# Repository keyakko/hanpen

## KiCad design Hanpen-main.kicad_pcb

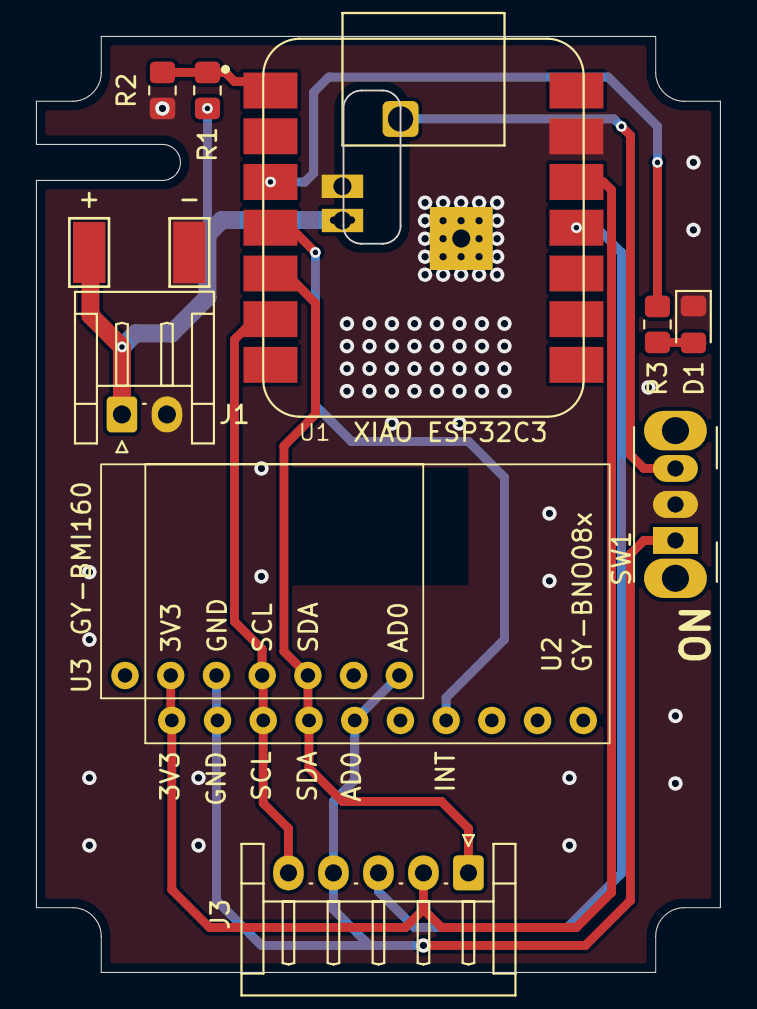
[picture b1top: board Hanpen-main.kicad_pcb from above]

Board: 2 copper layers, 37.9 x 52.0 mm, 12 parts (0 on the bottom side), 12 nets.

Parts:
+: TestPoint; TestPoint_Keystone_5015_Micro-Minature
-: TestPoint; TestPoint_Keystone_5015_Micro-Minature
D1: LED; LED_0805_2012Metric_Pad1.15x1.40mm_HandSolder
J1: Battery_Conn; JST_EH_S2B-EH_1x02_P2.50mm_Horizontal
J3: Sub_Sensor; JST_EH_S5B-EH_1x05_P2.50mm_Horizontal
R1, R2: 220K; R_0805_2012Metric_Pad1.20x1.40mm_HandSolder
R3: 220; R_0805_2012Metric_Pad1.20x1.40mm_HandSolder
SW1: SW; SW_Slide_SPDT_Angled_CK_OS102011MA1Q
U1: Seeed Studio XIAO ESP32C3; XIAO-ESP32C3-14P-2.54-21X17.8MM
U2: GY-BNO08x; GY-BN08X
U3: GY-BMI160; GY-BMI160_1

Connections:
+3.3V: J3.2, U1.12 (3V3), U2.1, U3.2
BAT+: +.1, J1.1, R1.1, U1.22 (BAT+)
BAT-: -.1, D1.1 (K), J1.2, R2.2, SW1.2 (B), U1.13 (GND), U1.21 (BAT-)
BATTERY_TEST: R1.2, R2.1, U1.1 (GPIO2_A0_D0)
EN: SW1.3 (C), U1.17 (EN)
INT1: U1.4 (GPIO5_A3_D3), U2.7
INT2: J3.3, U1.11 (GPIO10_D10_MOSI)
LED_OUT: R3.1, U1.3 (GPIO4_A2_D2)
unnamed: D1.2 (A), R3.2
SCL: J3.5, U1.6 (GPIO7_D5_SCL), U2.3, U3.4
SDA: J3.1, U1.5 (GPIO6_D4_SDA), U2.4, U3.5
SENSOR_GND: J3.4, SW1.1 (A), U2.2, U2.5, U3.3, U3.7

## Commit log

2025-03-18 add PCB data
2025-03-18 add case 3d model for main tracker
